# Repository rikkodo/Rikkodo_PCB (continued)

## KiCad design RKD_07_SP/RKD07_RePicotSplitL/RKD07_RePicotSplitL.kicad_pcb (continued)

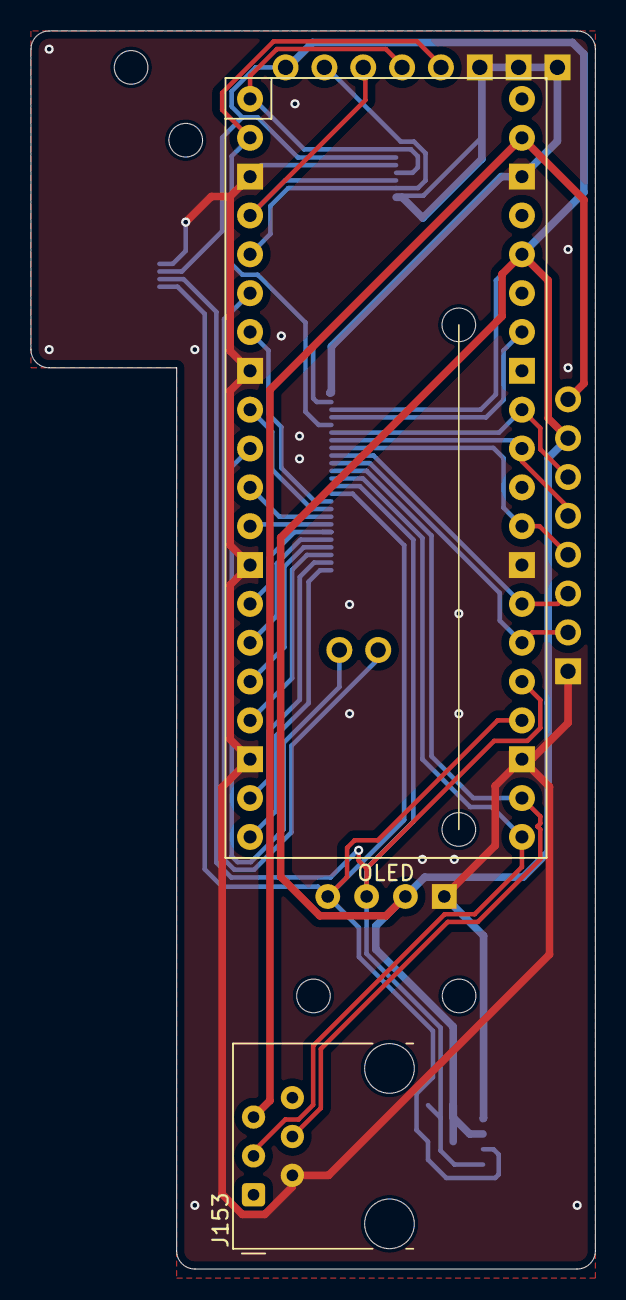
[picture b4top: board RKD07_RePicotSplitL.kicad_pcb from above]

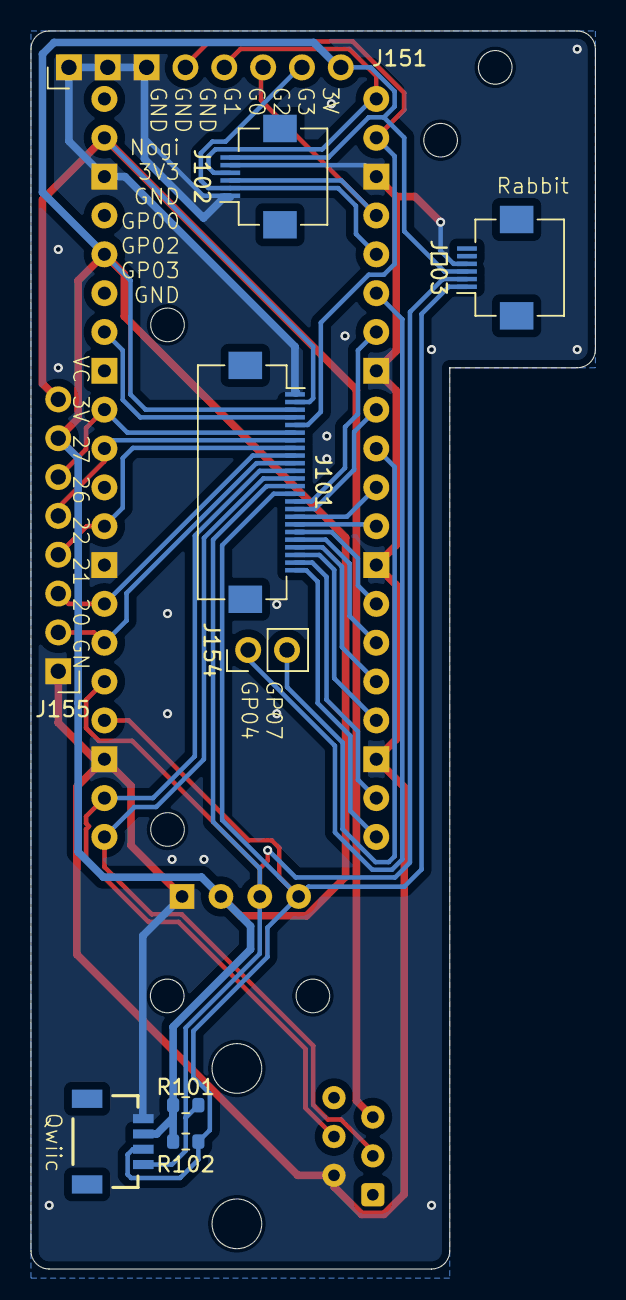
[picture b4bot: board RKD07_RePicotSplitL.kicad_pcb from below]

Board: 2 copper layers, 36.9 x 81.0 mm, 16 parts (9 on the bottom side), 29 nets.

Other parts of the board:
Point1: Guard_Screw_Hall; rkd_Guard_Screw_Hall
Ref**: Val**; m2_Screw_Hole
Ref**#2: Val**; m2_Screw_Hole
UnifiedW**: rkd_unified_wid_BTM
